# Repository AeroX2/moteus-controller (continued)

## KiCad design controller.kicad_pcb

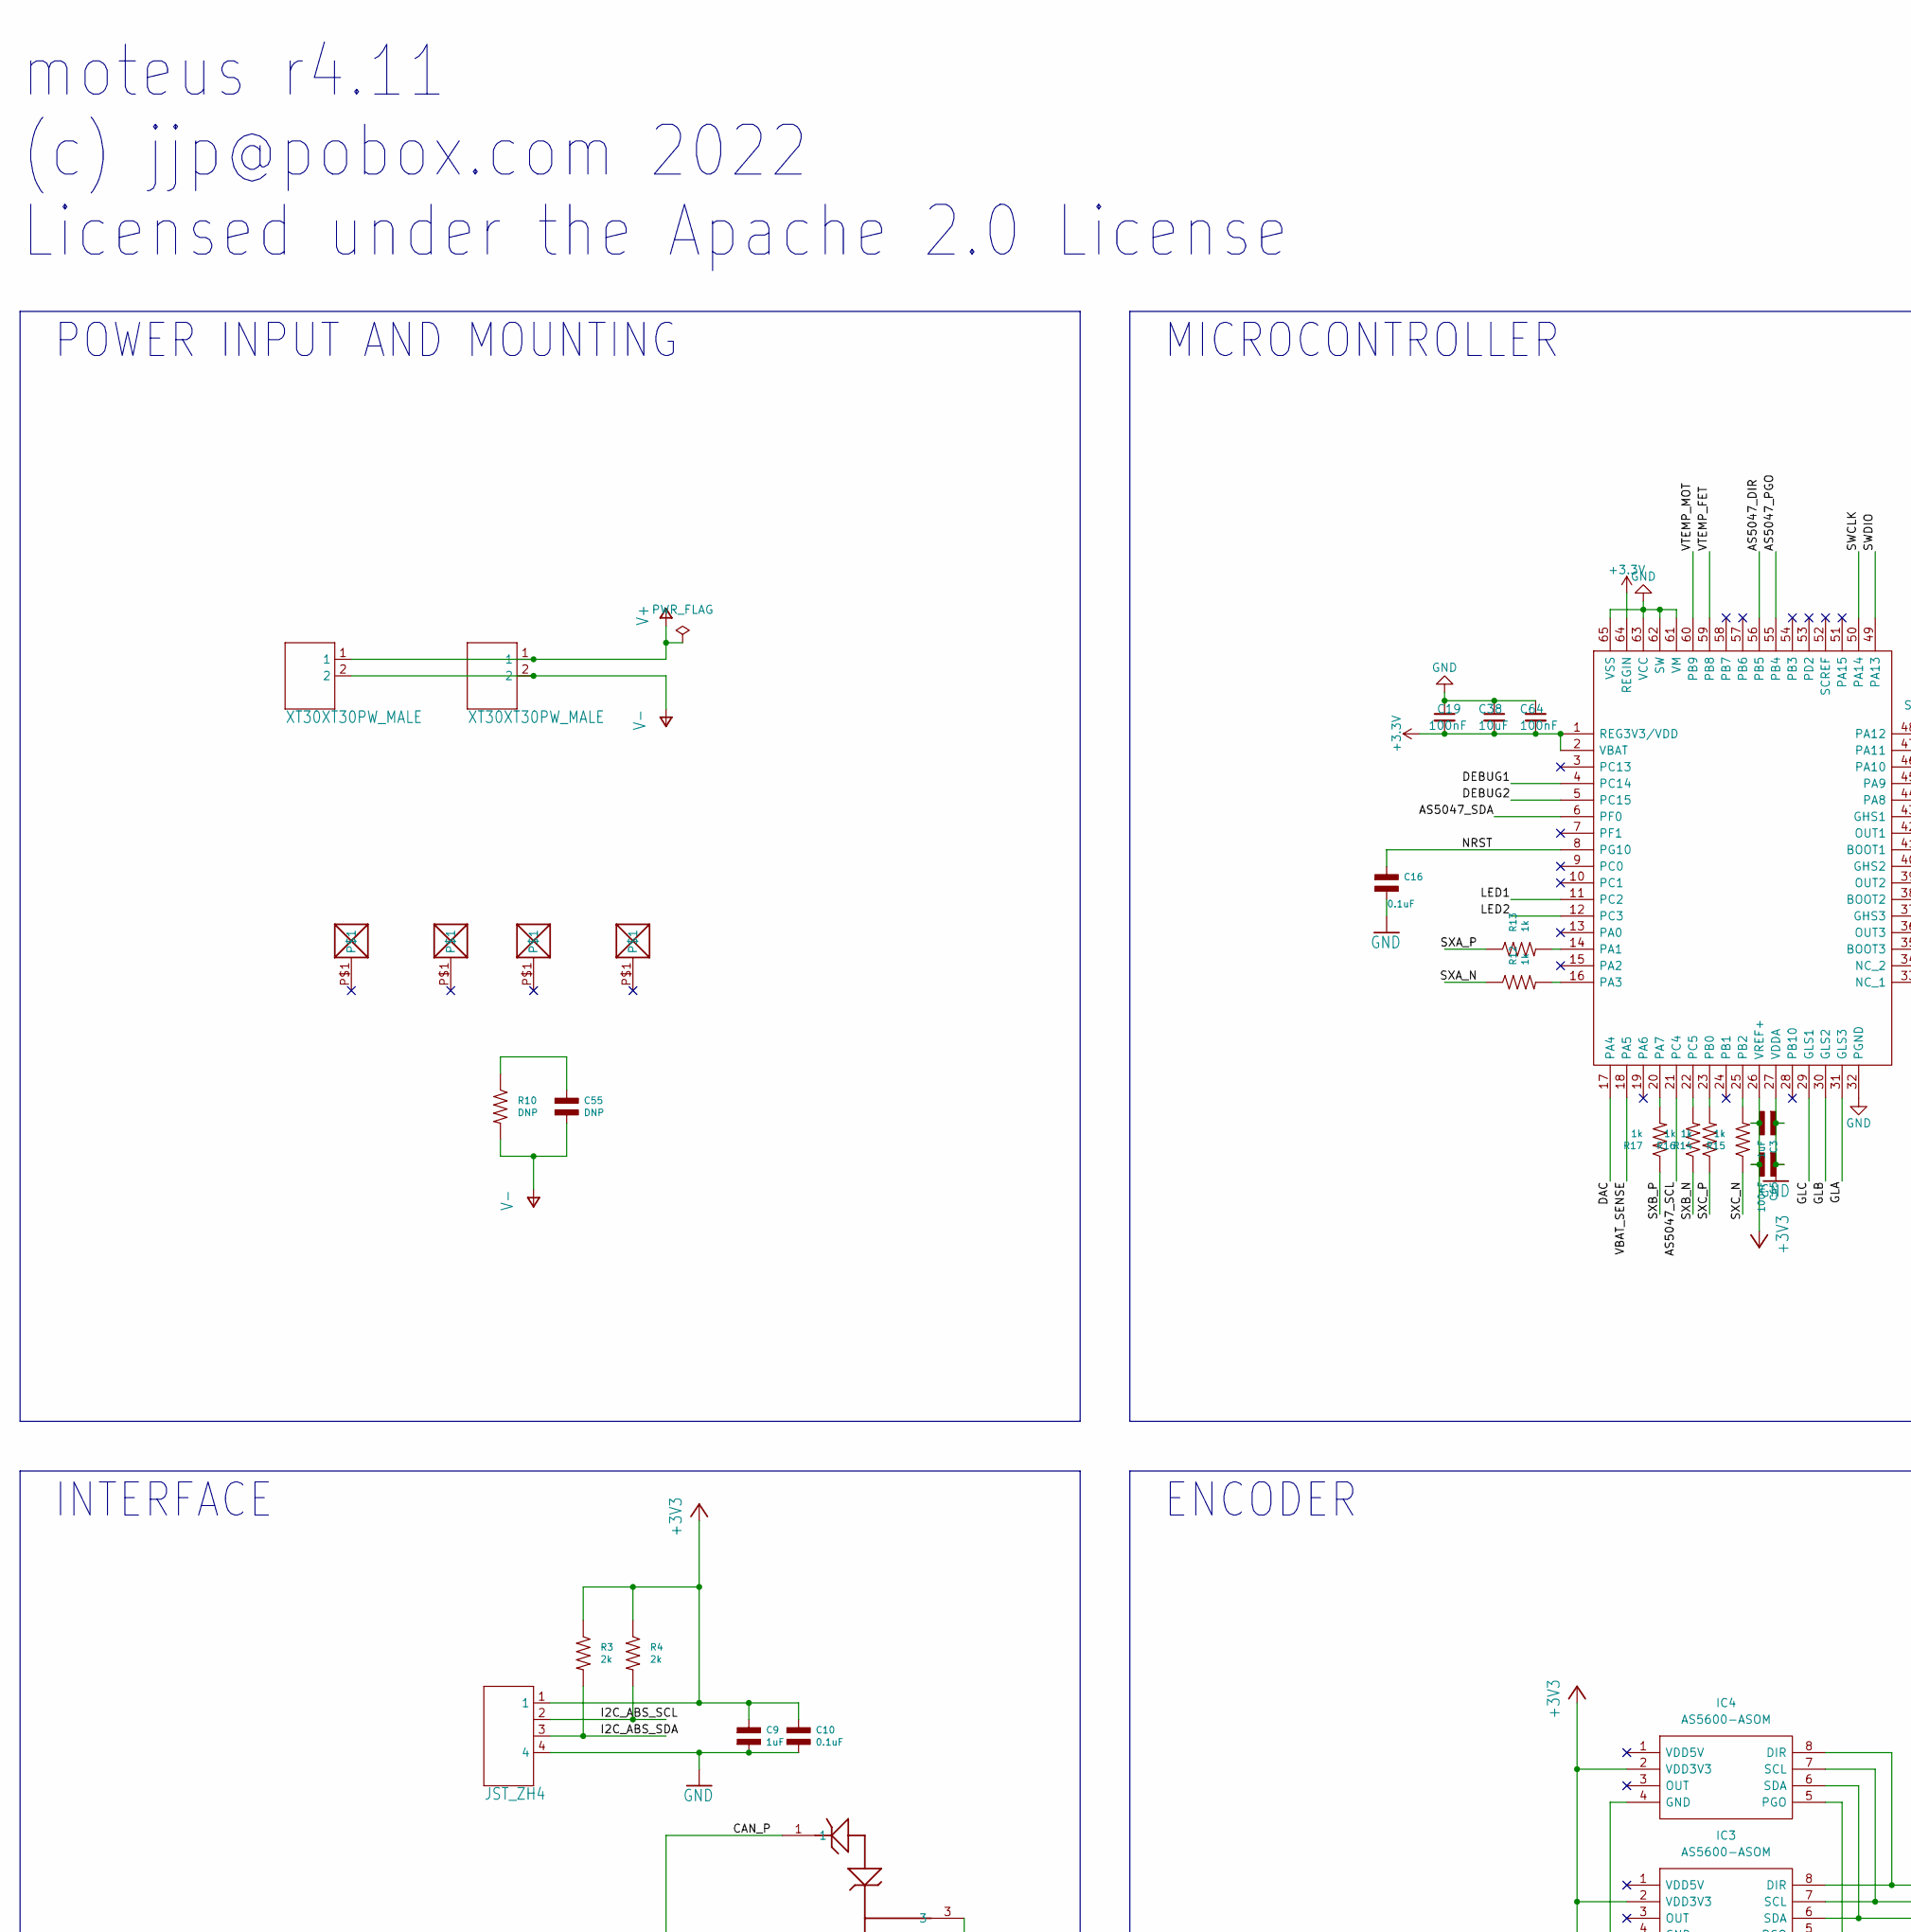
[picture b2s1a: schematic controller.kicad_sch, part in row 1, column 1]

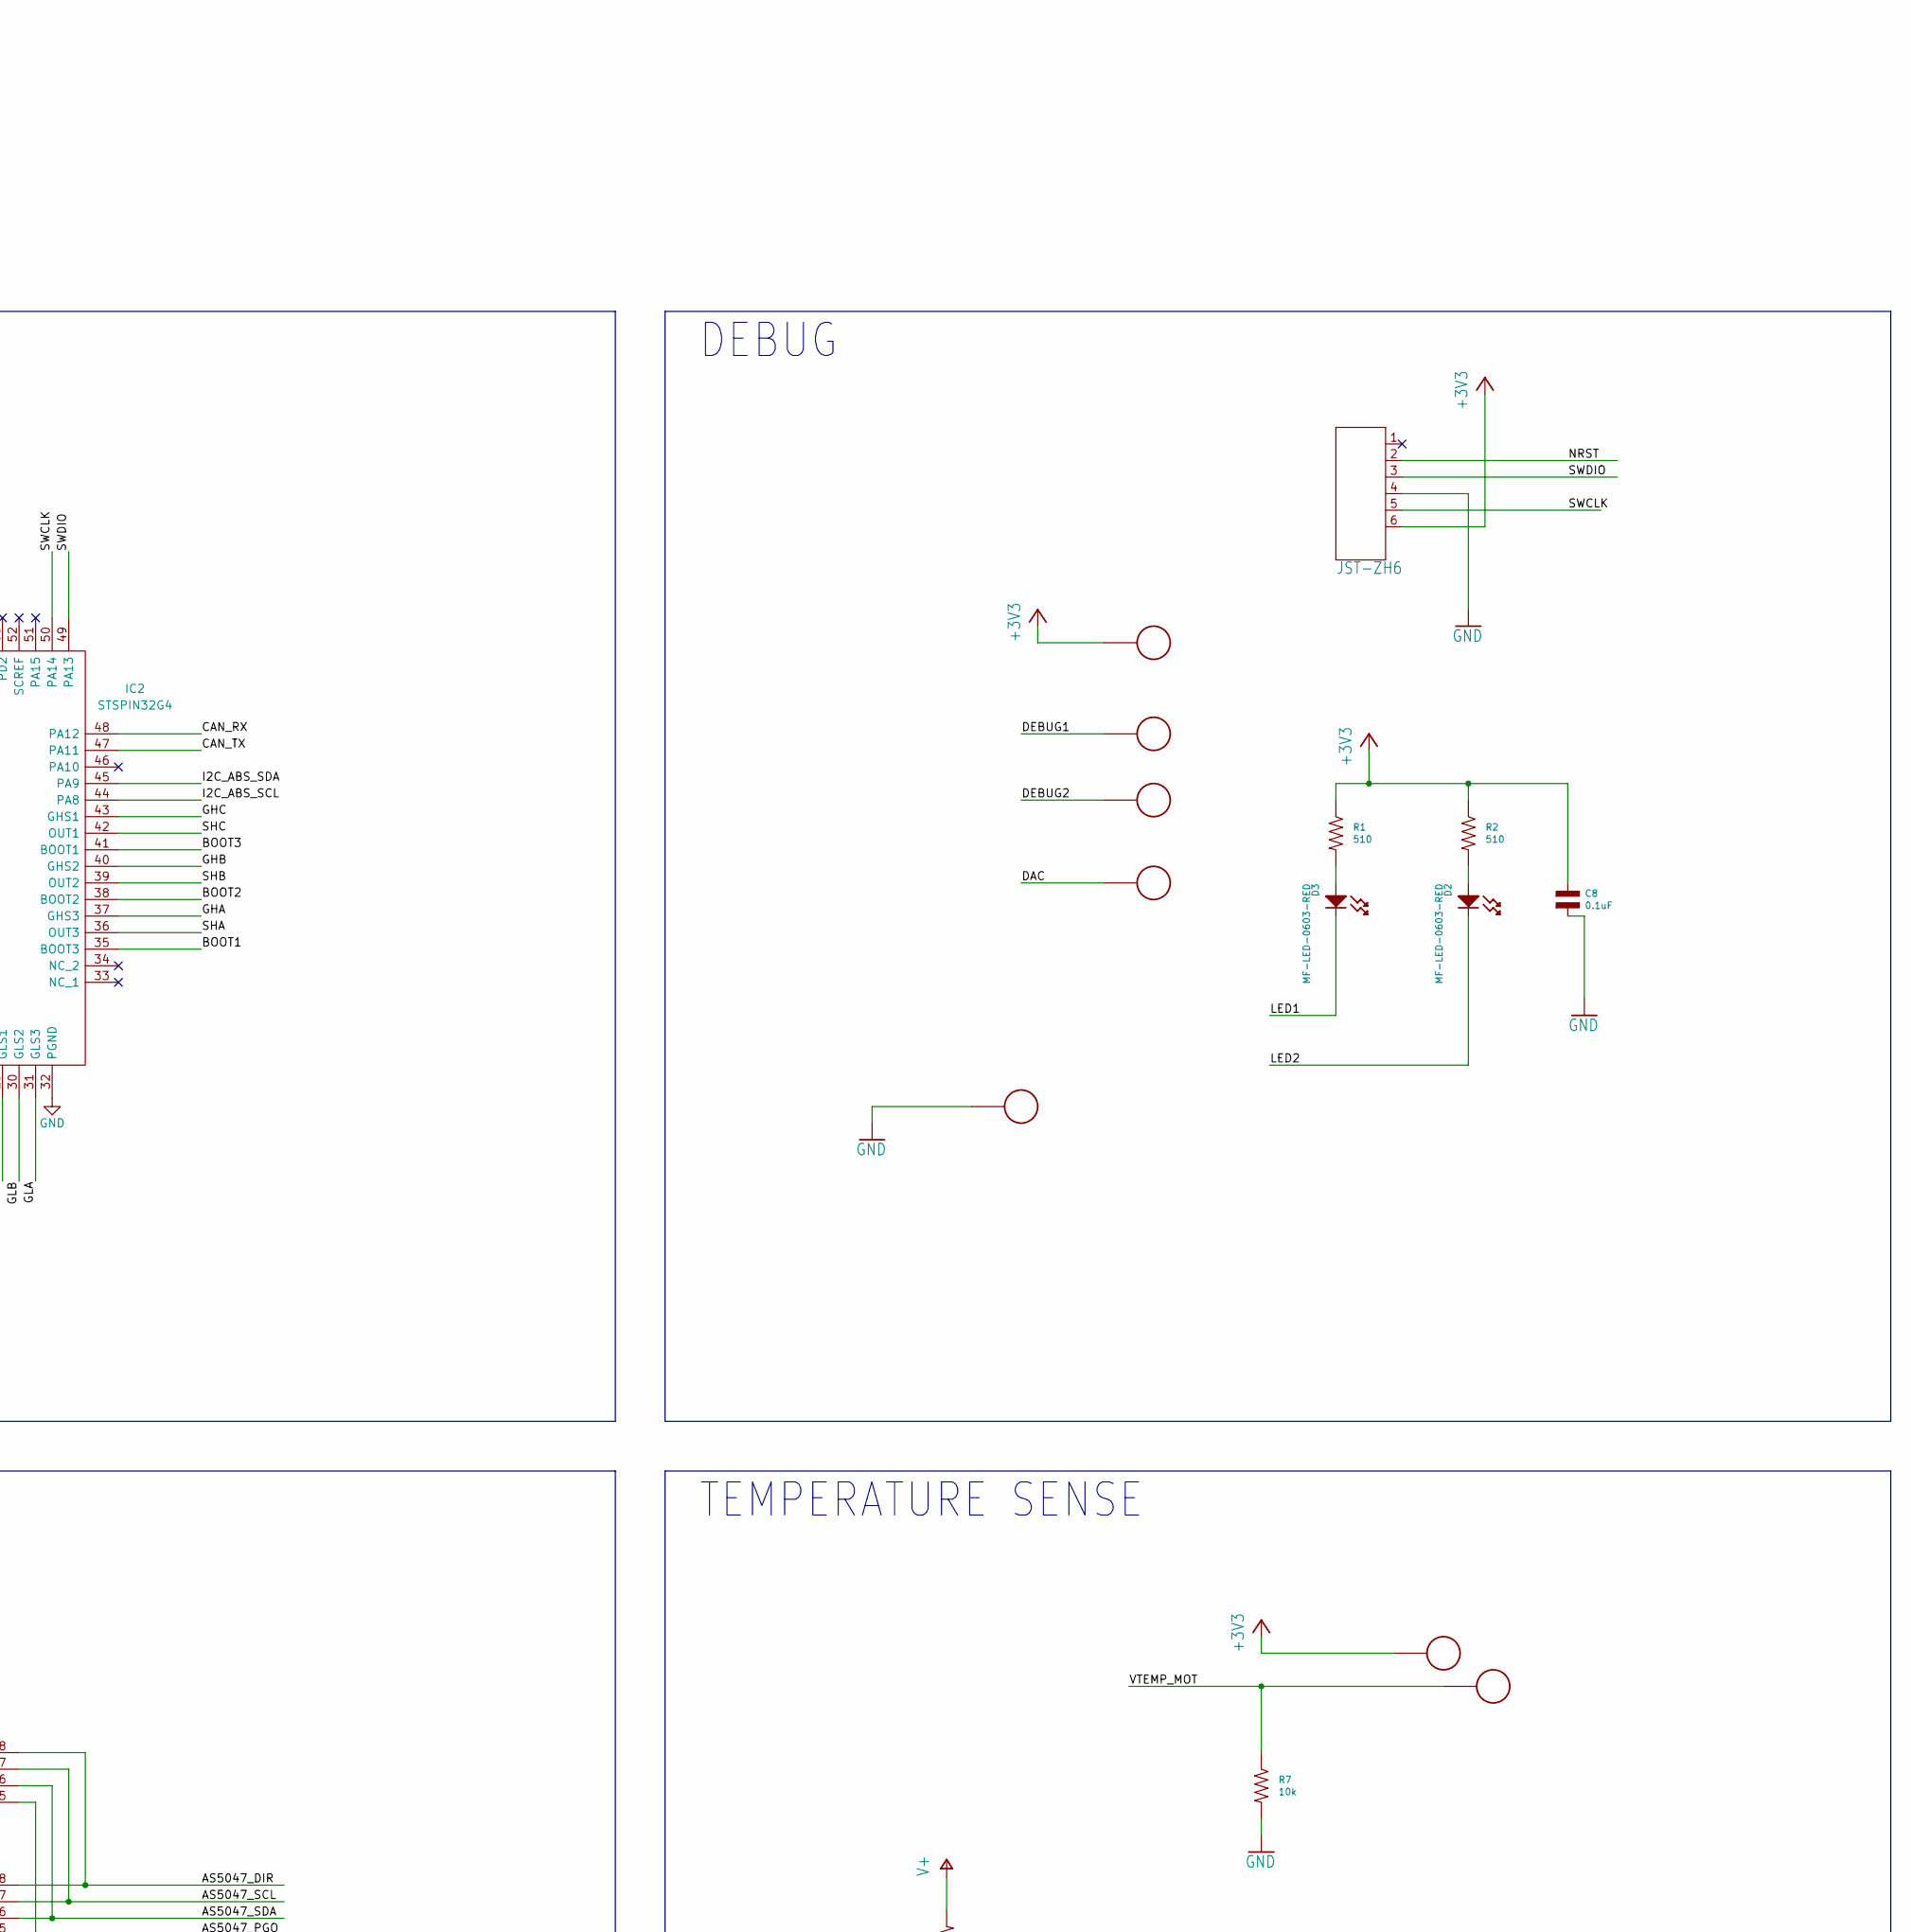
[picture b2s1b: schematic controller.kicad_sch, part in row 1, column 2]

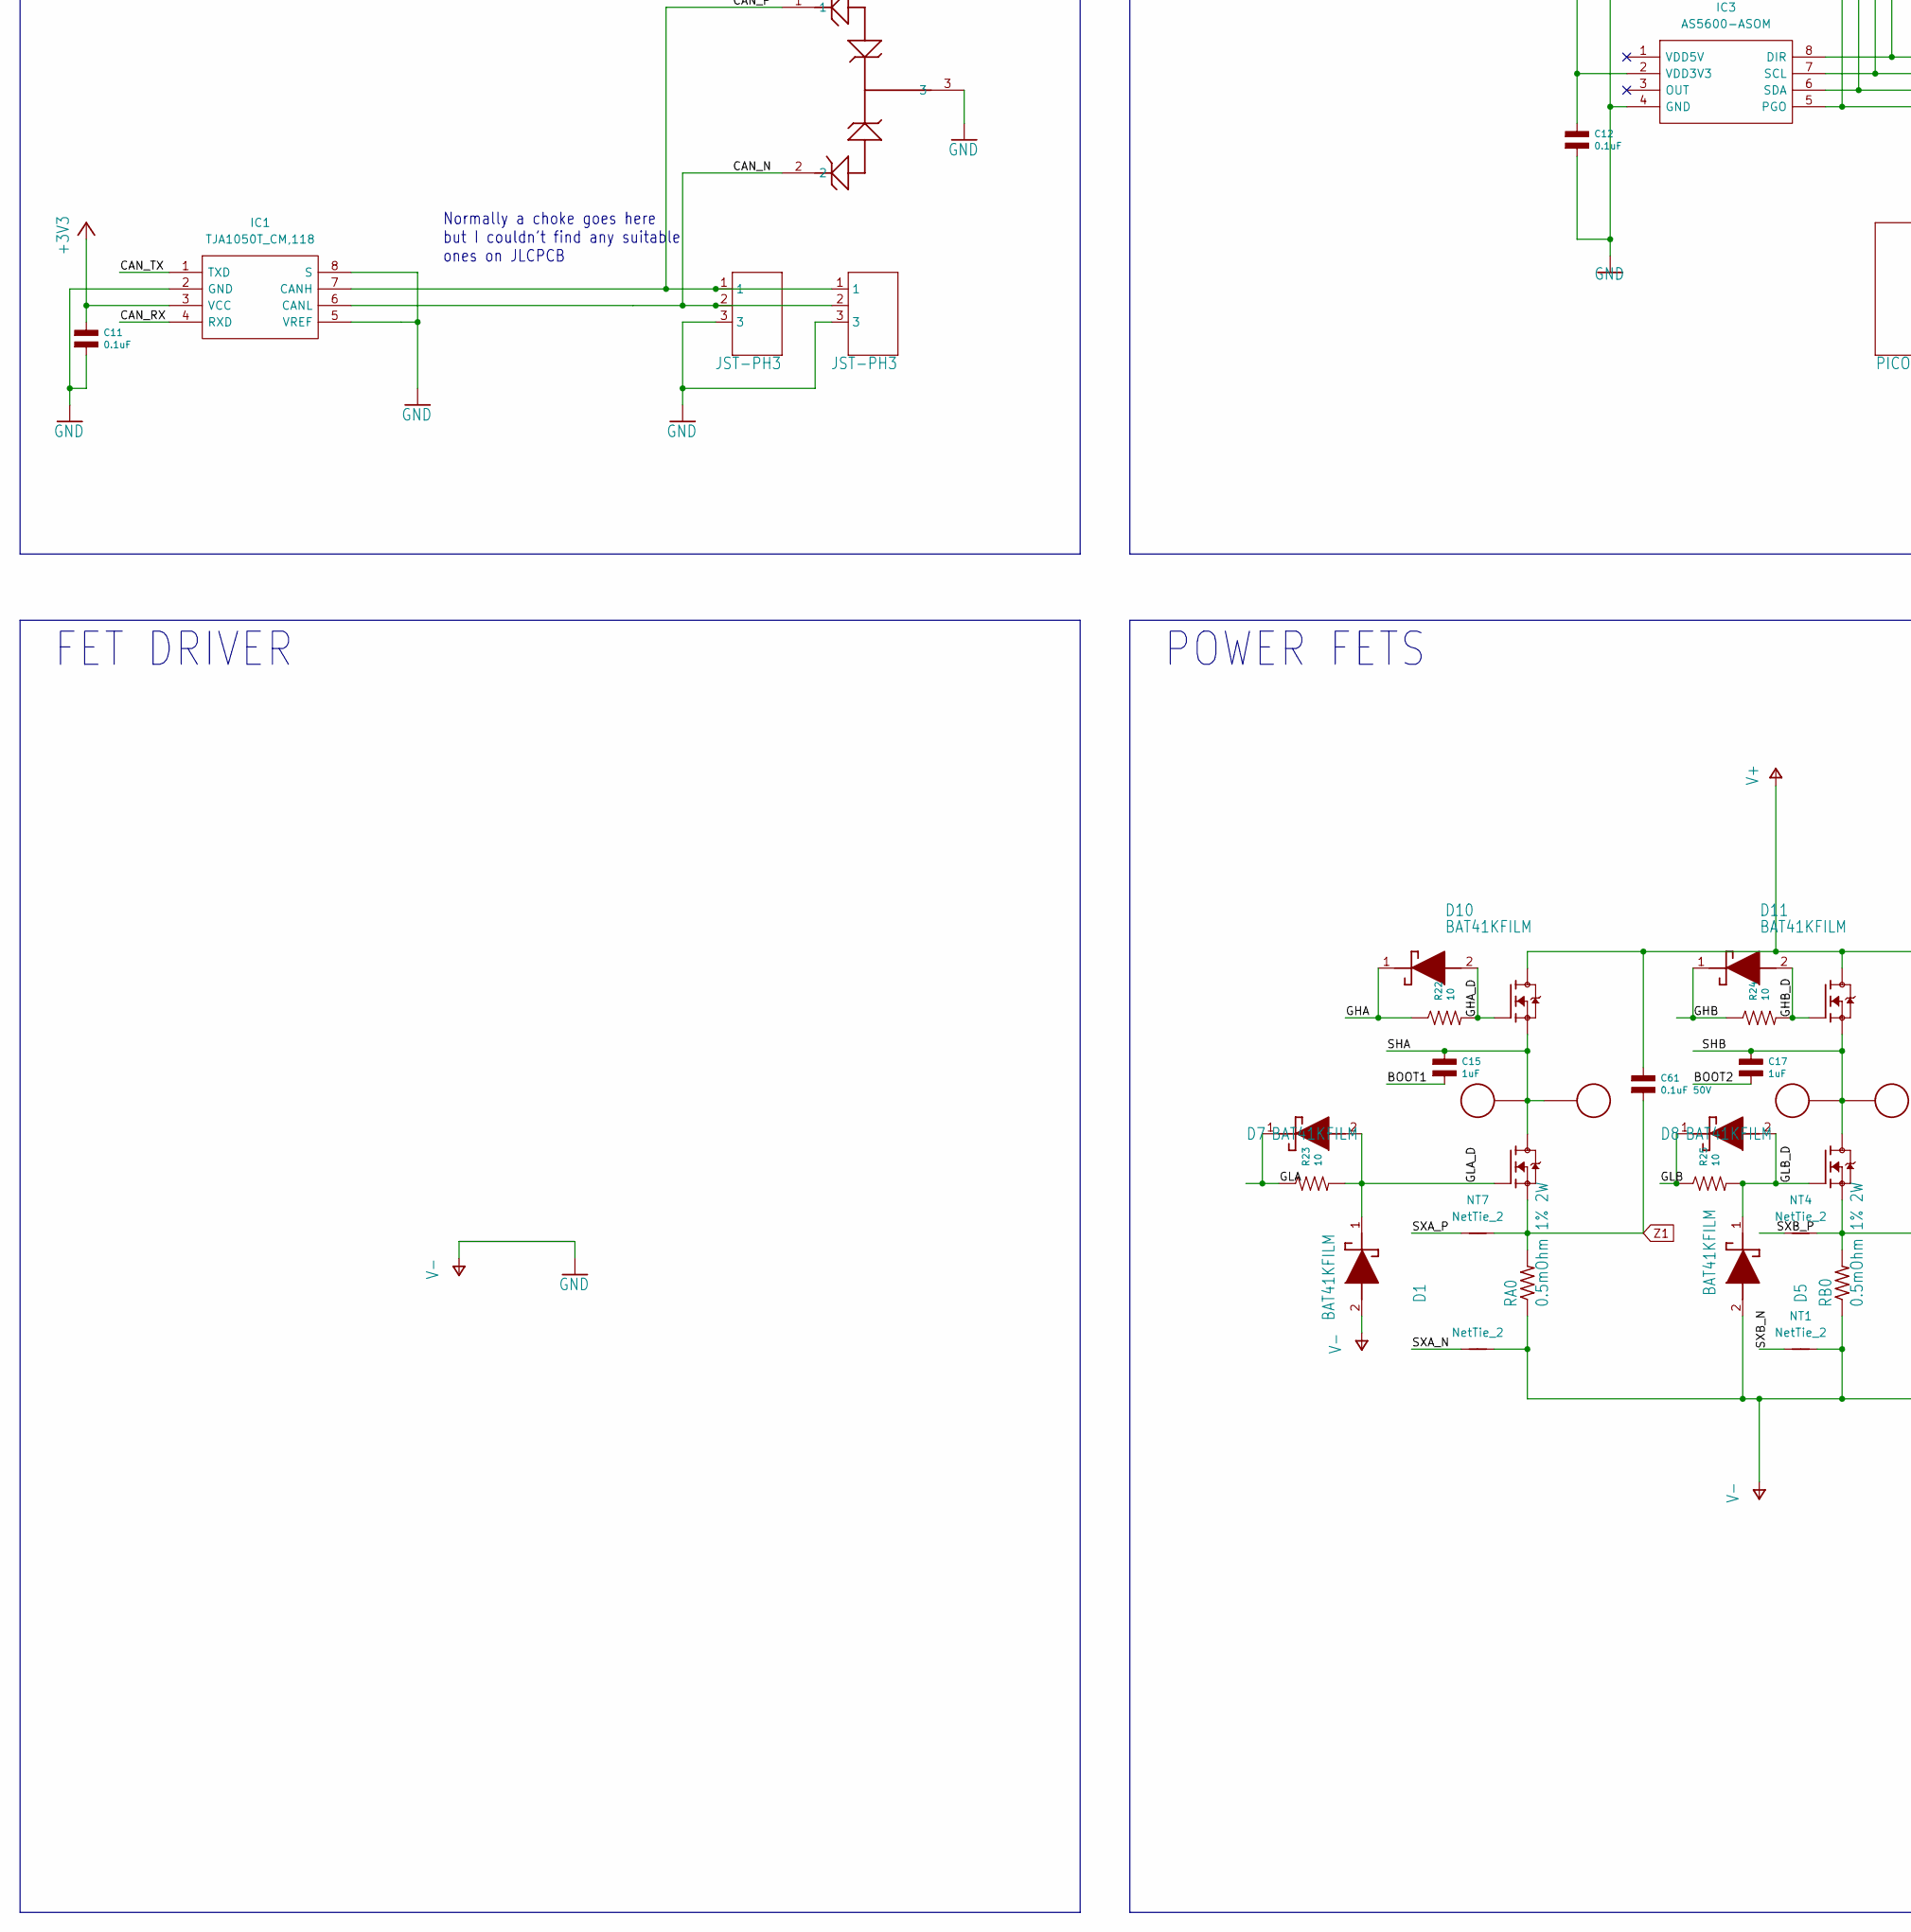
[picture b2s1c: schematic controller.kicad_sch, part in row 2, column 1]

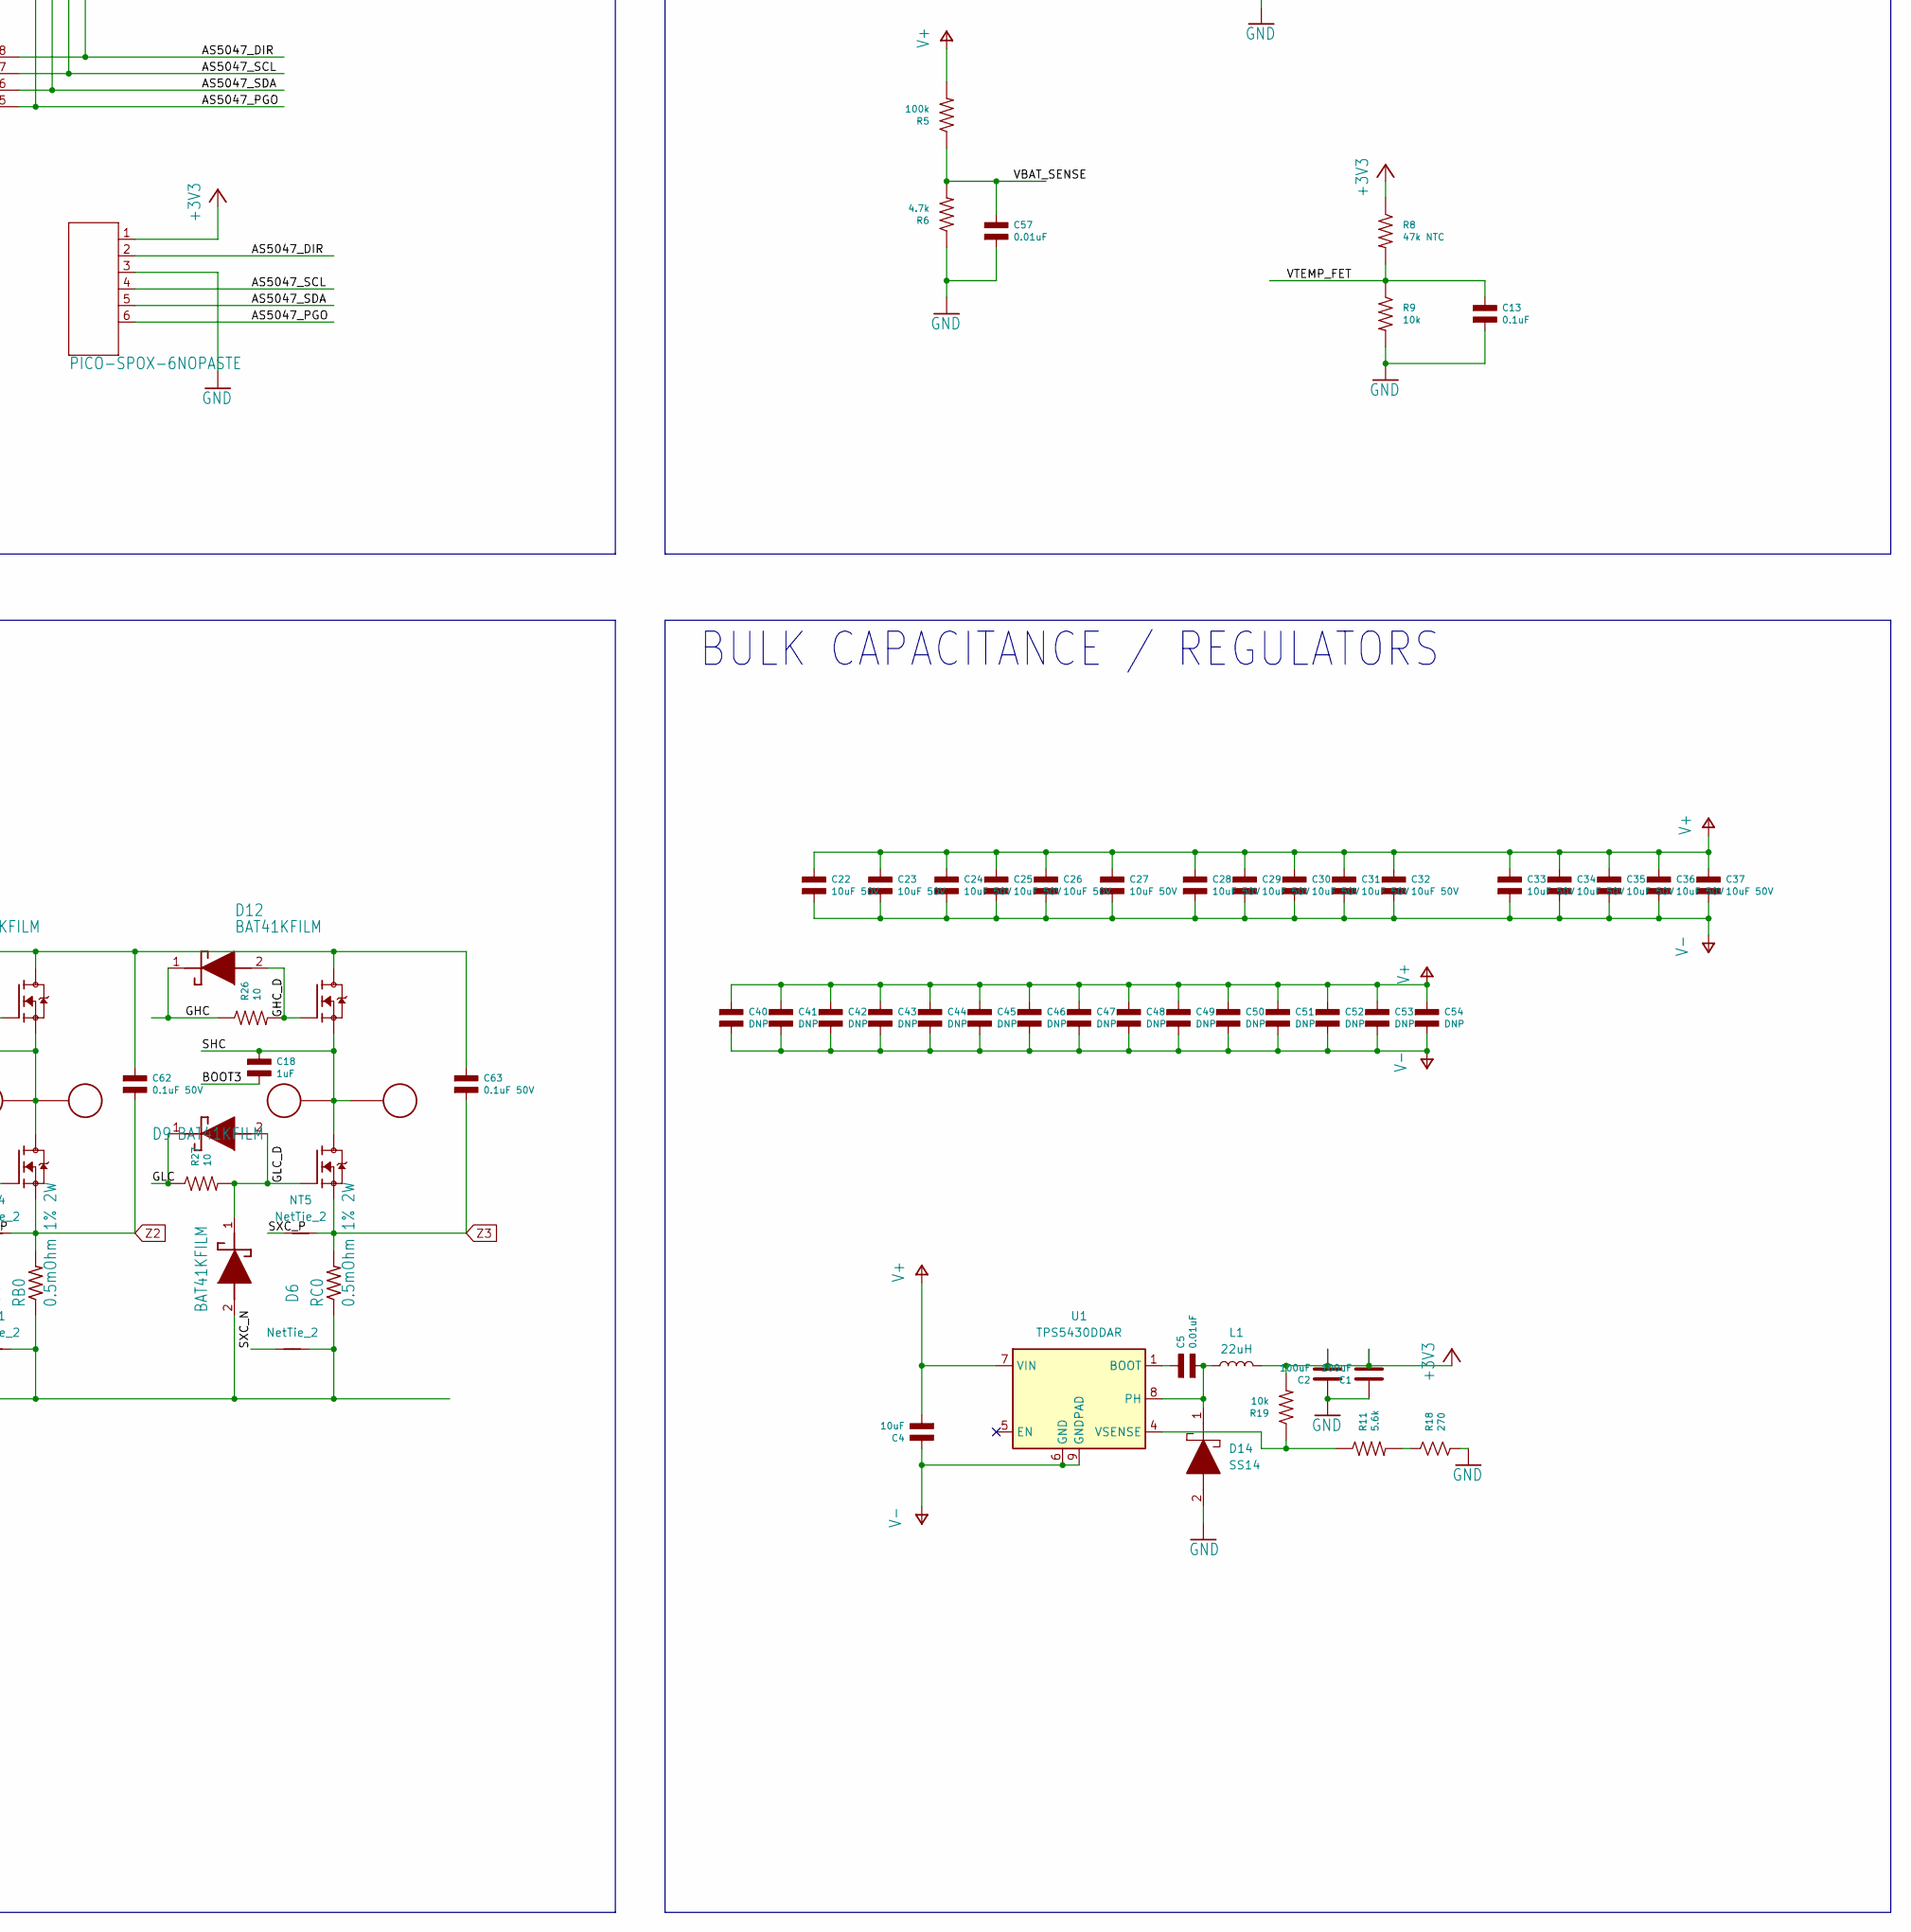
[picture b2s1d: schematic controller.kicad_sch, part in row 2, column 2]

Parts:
A0: PAD16AWG_PAD; 16AWG_PAD
ABS0: JST_ZH4; JST_S4B-ZR-SM4A-TF(LF)(SN); MPN S4B-ZR-SM4A-TF(LF)(SN)
B0: PAD16AWG_PAD; 16AWG_PAD
C0: PAD16AWG_PAD; 16AWG_PAD
C1, C2: 100uF; C_1206_3216Metric; MPN MF-CAP-0402-1uF
C3, C9, C15, C17, C18: 1uF; C0402; MPN MF-CAP-0402-1uF
C4: 10uF; C0805; MPN MF-CAP-0402-1uF
C5: 0.01uF; C0402; MPN MF-CAP-0402-1uF
C8, C10, C12, C13, C16: 0.1uF; C0402; MPN MF-CAP-0402-0.1uF
C11: 0.1uF; C0402_NOBORDER; MPN MF-CAP-0402-0.1uF
C19, C64: 100nF; C_0402_1005Metric
C22, C23, C24, C25, C26, C27, C28, C29, C30, C31, C32, C33, C34, C36, C37: 10uF 50V; C1206; MPN C3216X7R1H106K160AE
C35: 10uF 50V; C1206_NOBORDER; MPN C3216X7R1H106K160AE
C38: 10uF; C_0402_1005Metric
C40, C41, C42, C43, C44, C45, C46, C47, C48, C49, C50, C51, C52, C53, C54: DNP; C1206_NOCREAM
C55: DNP; C0402
C57: 0.01uF; C0402; MPN MF-CAP-0402-0.01uF
C61, C63: 0.1uF 50V; C1206; MPN 12065C104KAZ2A
C62: 0.1uF 50V; C0603_NOBORDER; MPN 06035C104KAZ2A
C65: 100nF; C0402; MPN MF-CAP-0402-1uF
CAN1, CAN2: JST-PH3; JST_S3B-PH-SM4-TB(LF)(SN); MPN S3B-PH-SM4-TB(LF)(SN)
D1, D5, D6, D7, D8, D9, D10, D11, D12: BAT41KFILM; SODFL1608X70N; MPN BAT41KFILM
D2: MF-LED-0603-RED; LED0603; MPN MF-LED-0603-GREEN
D3: MF-LED-0603-RED; LED0603
D4: DUAL_TVS; SOT23-3; MPN CDSOT23-0502B
D14: SS14; DIOM5127X261N; Manufacturer_Part_Number SS14
D33: PAD24AWG_PAD; 24AWG_PAD
DA0: PAD24AWG_PAD; 24AWG_PAD
DAC0: PAD24AWG_PAD; 24AWG_PAD
DB0: PAD24AWG_PAD; 24AWG_PAD
DBG1, DBG2: PAD24AWG_PAD; 24AWG_PAD
DC0: PAD24AWG_PAD; 24AWG_PAD
DG2: PAD24AWG_PAD; 24AWG_PAD
ENC0: PICO-SPOX-6NOPASTE; PICO-SPOX-SMT-RA-6-NOPASTE
IC1: TJA1050T_CM,118; SOIC127P600X175-8N; Manufacturer_Part_Number TJA1050T/CM,118; Mouser Part Number 771-TJA1050T/CM118
IC2: STSPIN32G4; QFN50P900X900X100-65N-D; Manufacturer_Part_Number STSPIN32G4; Mouser Part Number 511-STSPIN32G4
IC3, IC4: AS5600-ASOM; SOIC127P600X175-8N; Manufacturer_Part_Number AS5600-ASOM; Mouser Part Number 985-AS5600-ASOM
J1, J2: XT30XT30PW_MALE; XT30PW_MALE
L1: 22uH; L_0805_2012Metric
M1, M2, M3, M4: MOUNT; MountingHole_2.7mm_M2.5_DIN965_Pad
NT1, NT4, NT5, NT6, NT7, NT8: NetTie_2; NetTie-2_SMD_Pad0.2mm
Q1, Q3, Q5: TPH1R204PLSOP_ADVANCE_8; SOP_ADVANCE_8; MPN TPH2R506PL,L1Q
Q2, Q4, Q6: TPH1R204PLSOP_ADVANCE_8; SOP_ADVANCE_8; MPN TPH4R50ANH,L1Q(M
R1, R2: 510; R0402; MPN MF-RES-0402-560
R3, R4: 2k; R0402; MPN MF-RES-0402-2K
R5: 100k; R0402; MPN RC0402FR-07100KL
R6: 4.7k; R0402; MPN RC0402FR-074K7L
R7, R9, R19: 10k; R0402; MPN RC0402FR-0710KL
R8: 47k NTC; R0402; MPN NCP15WB473F03RC
R10: DNP; R0402
R11: 5.6k; R0402; MPN RC0402FR-0710KL
R12, R13, R14, R15, R16, R17: 1k; R0402; MPN MF-RES-0402-2K
R18: 270; R_0603_1608Metric; MPN RC0402FR-0710KL
R22, R23, R24, R25, R26, R27: 10; R0402; MPN RC0402FR-077R5L
RA0: 0.5mOhm 1% 2W; M1206; MPN HCS1206FTL500
RB0: 0.5mOhm 1% 2W; M1206; MPN HCS1206FTL500
RC0: 0.5mOhm 1% 2W; M1206; MPN HCS1206FTL500
SWD0: JST-ZH6; JST_S6B-ZR-SM4A-TF(LF)(SN); MPN S6B-ZR-SM4A-TF(LF)(SN)
TEMP1, TEMP2: PAD24AWG_PAD; 24AWG_PAD
U1: TPS5430DDAR; TI_SO-PowerPAD-8_ThermalVias

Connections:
/AS5047_DIR: ENC0.2, IC2.56 (PB5), IC3.8 (DIR), IC4.8 (DIR)
/AS5047_PGO: ENC0.6, IC2.55 (PB4), IC3.5 (PGO), IC4.5 (PGO)
/AS5047_SCL: ENC0.4, IC2.21 (PC4), IC3.7 (SCL), IC4.7 (SCL)
/AS5047_SDA: ENC0.5, IC2.6 (PF0), IC3.6 (SDA), IC4.6 (SDA)
/BOOT1: C15.P$2, IC2.35 (BOOT3)
/BOOT2: C17.P$2, IC2.38 (BOOT2)
/BOOT3: C18.P$2, IC2.41 (BOOT1)
/CAN_N: CAN1.2, CAN2.2, D4.2, IC1.6 (CANL)
/CAN_P: CAN1.1, CAN2.1, D4.1, IC1.7 (CANH)
/CAN_RX: IC1.4 (RXD), IC2.48 (PA12)
/CAN_TX: IC1.1 (TXD), IC2.47 (PA11)
/DAC: DAC0.P$1, IC2.17 (PA4)
/DEBUG1: DBG1.P$1, IC2.4 (PC14)
/DEBUG2: DBG2.P$1, IC2.5 (PC15)
/GHA: D10.1 (K), IC2.37 (GHS3), R22.P$1
/GHA_D: D10.2 (A), Q1.4 (G), R22.P$2
/GHB: D11.1 (K), IC2.40 (GHS2), R24.P$1
/GHB_D: D11.2 (A), Q3.4 (G), R24.P$2
/GHC: D12.1 (K), IC2.43 (GHS1), R26.P$1
/GHC_D: D12.2 (A), Q5.4 (G), R26.P$2
/GLA: D7.1 (K), IC2.31 (GLS3), R23.P$1
/GLA_D: D1.1 (K), D7.2 (A), Q2.4 (G), R23.P$2
/GLB: D8.1 (K), IC2.30 (GLS2), R25.P$1
/GLB_D: D5.1 (K), D8.2 (A), Q4.4 (G), R25.P$2
/GLC: D9.1 (K), IC2.29 (GLS1), R27.P$1
/GLC_D: D6.1 (K), D9.2 (A), Q6.4 (G), R27.P$2
/I2C_ABS_SCL: ABS0.2, IC2.44 (PA8), R4.P$2
/I2C_ABS_SDA: ABS0.3, IC2.45 (PA9), R3.P$2
/LED1: D3.CATHODE, IC2.11 (PC2)
/LED2: D2.CATHODE, IC2.12 (PC3)
/NRST: C16.P$1, IC2.8 (PG10), SWD0.2
/SHA: A0.1, C15.P$1, DA0.P$1, IC2.36 (OUT3), Q1.1 (S), Q1.2 (S), Q1.3 (S), Q2.5 (D), Q2.6 (D), Q2.7 (D), Q2.8 (D), Q2.PAD (D)
/SHB: B0.1, C17.P$1, DB0.P$1, IC2.39 (OUT2), Q3.1 (S), Q3.2 (S), Q3.3 (S), Q4.5 (D), Q4.6 (D), Q4.7 (D), Q4.8 (D), Q4.PAD (D)
/SHC: C0.1, C18.P$1, DC0.P$1, IC2.42 (OUT1), Q5.1 (S), Q5.2 (S), Q5.3 (S), Q6.5 (D), Q6.6 (D), Q6.7 (D), Q6.8 (D), Q6.PAD (D)
/SWCLK: IC2.50 (PA14), SWD0.5
/SWDIO: IC2.49 (PA13), SWD0.3
/SXA_N: NT8.1, R12.P$1
/SXA_P: NT7.1, R13.P$1
/SXB_N: NT1.1, R16.P$1
/SXB_P: NT4.1, R17.P$1
/SXC_N: NT6.1, R15.P$1
/SXC_P: NT5.1, R14.P$1
/VBAT_SENSE: C57.P$1, IC2.18 (PA5), R5.P$1, R6.P$2
/VTEMP_FET: C13.P$1, IC2.59 (PB8), R8.P$2, R9.P$1
/VTEMP_MOT: IC2.60 (PB9), R7.P$1, TEMP2.P$1
GND: ABS0.4, C1.1, C2.1, C3.P$1, C4.P$1, C8.P$2, C9.P$2, C10.P$2, C11.P$2, C12.P$2, C13.P$2, C16.P$2, C19.1, C22.P$2, C23.P$2, C24.P$2, C25.P$2, C26.P$2, C27.P$2, C28.P$2, C29.P$2, C30.P$2, C31.P$2, C32.P$2, C33.P$2, C34.P$2, C35.P$2, C36.P$2, C37.P$2, C38.1, C40.P$2, C41.P$2, C42.P$2, C43.P$2, C44.P$2, C45.P$2, C46.P$2, C47.P$2, C48.P$2, C49.P$2, C50.P$2, C51.P$2, C52.P$2, C53.P$2, C54.P$2, C55.P$2, C57.P$2, C64.1, C65.P$1, CAN1.3, CAN2.3, D1.2 (A), D4.3, D5.2 (A), D6.2 (A), D14.2, DG2.P$1, ENC0.3, IC1.2 (GND), IC1.5 (VREF), IC1.8 (S), IC2.27 (VDDA), IC2.32 (PGND), IC2.61 (VM), IC2.62 (SW), IC2.63 (VCC), IC2.65 (VSS), IC3.4 (GND), IC4.4 (GND), J1.2, J2.2, NT1.2, NT6.2, NT8.2, R6.P$1, R7.P$2, R9.P$2, R10.P$2, R18.2, RA0.1, RB0.1, RC0.1, SWD0.4, U1.6 (GND), U1.9 (GNDPAD)
unnamed: C55.P$1, R10.P$1
unnamed: D2.ANODE, R2.P$2
unnamed: D3.ANODE, R1.P$2
unnamed: IC2.14 (PA1), R13.P$2
unnamed: IC2.16 (PA3), R12.P$2
unnamed: IC2.20 (PA7), R17.P$2
unnamed: IC2.23 (PB0), R14.P$2
unnamed: IC2.25 (PB2), R15.P$2
unnamed: IC2.22 (PC5), R16.P$2
unnamed: R11.P$2, R18.1
unnamed: C5.P$1, U1.1 (BOOT)
unnamed: C5.P$2, D14.1, L1.1, U1.8 (PH)
unnamed: R11.P$1, R19.P$1, U1.4 (VSENSE)
V+: C4.P$2, C22.P$1, C23.P$1, C24.P$1, C25.P$1, C26.P$1, C27.P$1, C28.P$1, C29.P$1, C30.P$1, C31.P$1, C32.P$1, C33.P$1, C34.P$1, C35.P$1, C36.P$1, C37.P$1, C40.P$1, C41.P$1, C42.P$1, C43.P$1, C44.P$1, C45.P$1, C46.P$1, C47.P$1, C48.P$1, C49.P$1, C50.P$1, C51.P$1, C52.P$1, C53.P$1, C54.P$1, C61.P$1, C62.P$1, C63.P$1, J1.1, J2.1, Q1.5 (D), Q1.6 (D), Q1.7 (D), Q1.8 (D), Q1.PAD (D), Q3.5 (D), Q3.6 (D), Q3.7 (D), Q3.8 (D), Q3.PAD (D), Q5.5 (D), Q5.6 (D), Q5.7 (D), Q5.8 (D), Q5.PAD (D), R5.P$2, U1.7 (VIN)
Z1: C61.P$2, NT7.2, Q2.1 (S), Q2.2 (S), Q2.3 (S), RA0.2
Z2: C62.P$2, NT4.2, Q4.1 (S), Q4.2 (S), Q4.3 (S), RB0.2
Z3: C63.P$2, NT5.2, Q6.1 (S), Q6.2 (S), Q6.3 (S), RC0.2

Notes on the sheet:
DEBUG
POWER FETS
moteus r4.11 (c) jjp@pobox.com 2022 Licensed under the Apache 2.0 License
ENCODER
BULK CAPACITANCE / REGULATORS
INTERFACE
MICROCONTROLLER
FET DRIVER
Normally a choke goes here but I couldn't find any suitable ones on JLCPCB
TEMPERATURE SENSE
POWER INPUT AND MOUNTING

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
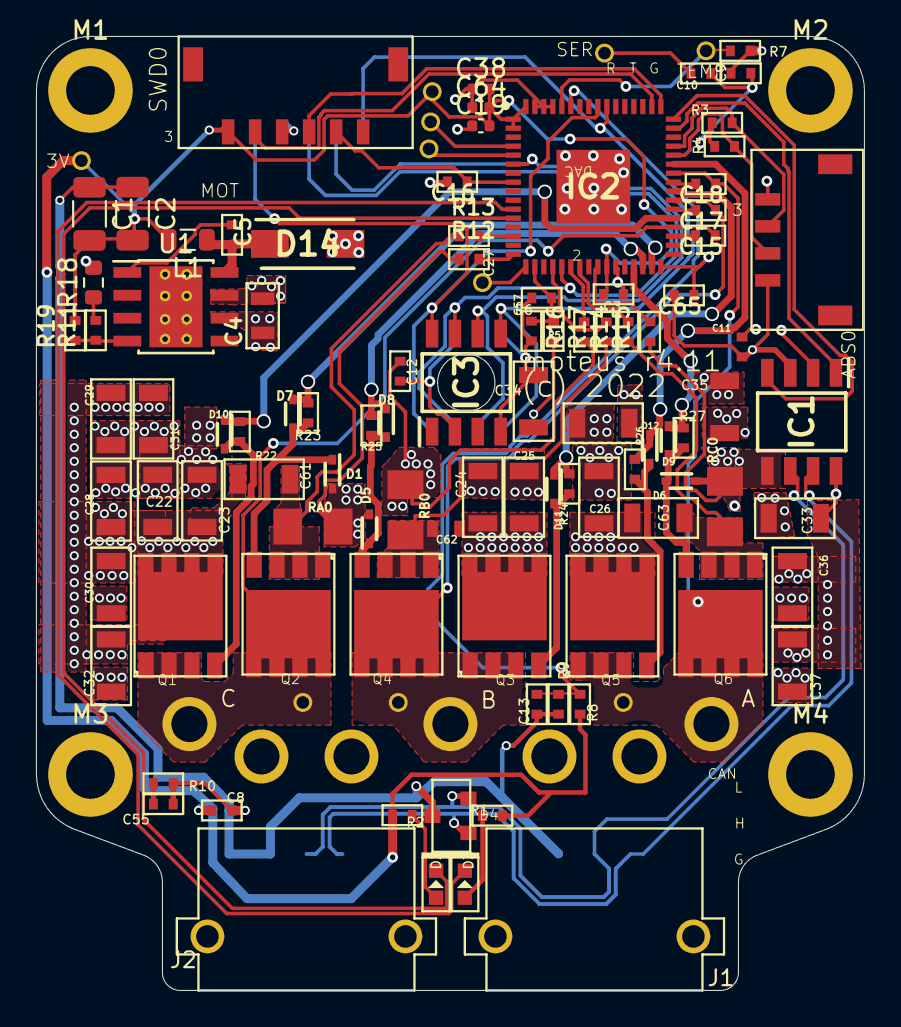
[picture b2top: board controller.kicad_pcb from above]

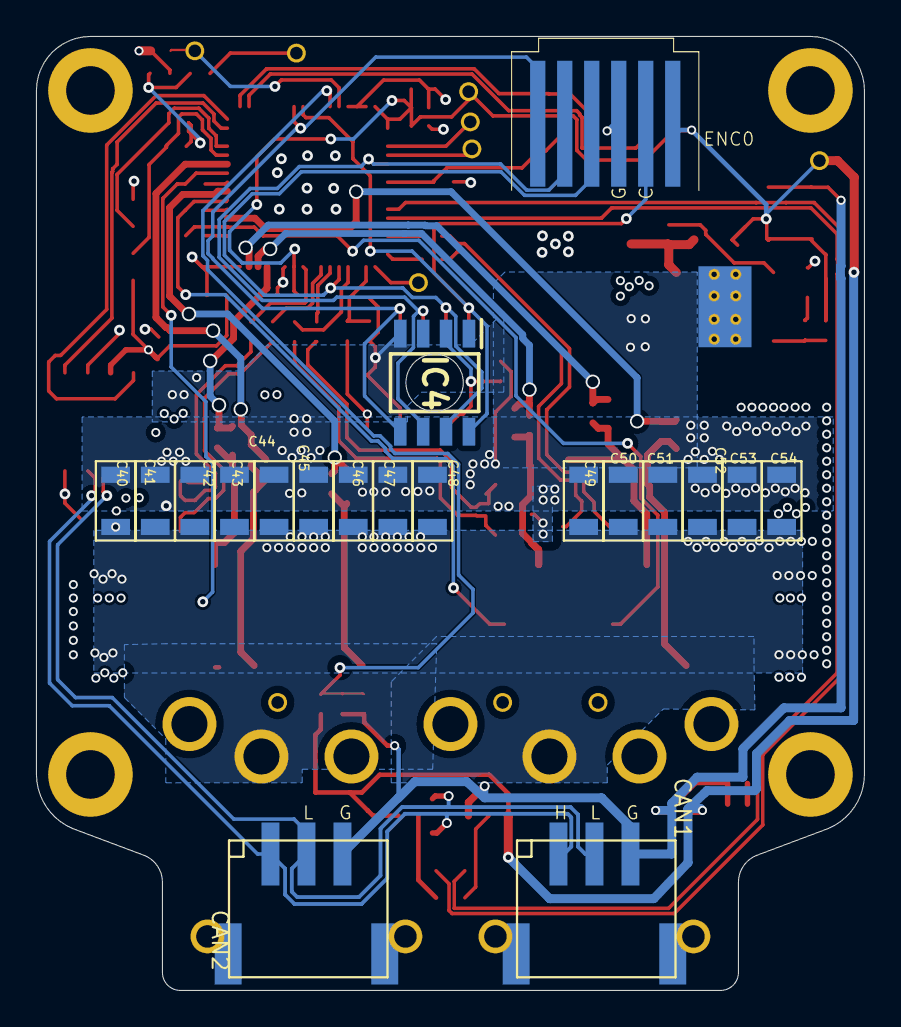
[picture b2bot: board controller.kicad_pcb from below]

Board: 4 copper layers, 46.0 x 53.0 mm, 138 parts (19 on the bottom side), 64 nets.

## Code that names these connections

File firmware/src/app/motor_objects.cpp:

#include "app/app_context.h"

MagneticSensorSPI magnetic_sensor = MagneticSensorSPI(AS5048_SPI, PD2);
SPIClass spi_class(PB5, PB4, PB3);

// (gain values comes from B-G431B-ESC1, multiplied by 10 because that is what worked)
LowsideCurrentSense current_sense = LowsideCurrentSense(0.01f, -64.0f / 7.0f * 10.0f, PB1, _NC, PA2);

STSPIN32G4 driver = STSPIN32G4();
BLDCMotor motor = BLDCMotor(7);
